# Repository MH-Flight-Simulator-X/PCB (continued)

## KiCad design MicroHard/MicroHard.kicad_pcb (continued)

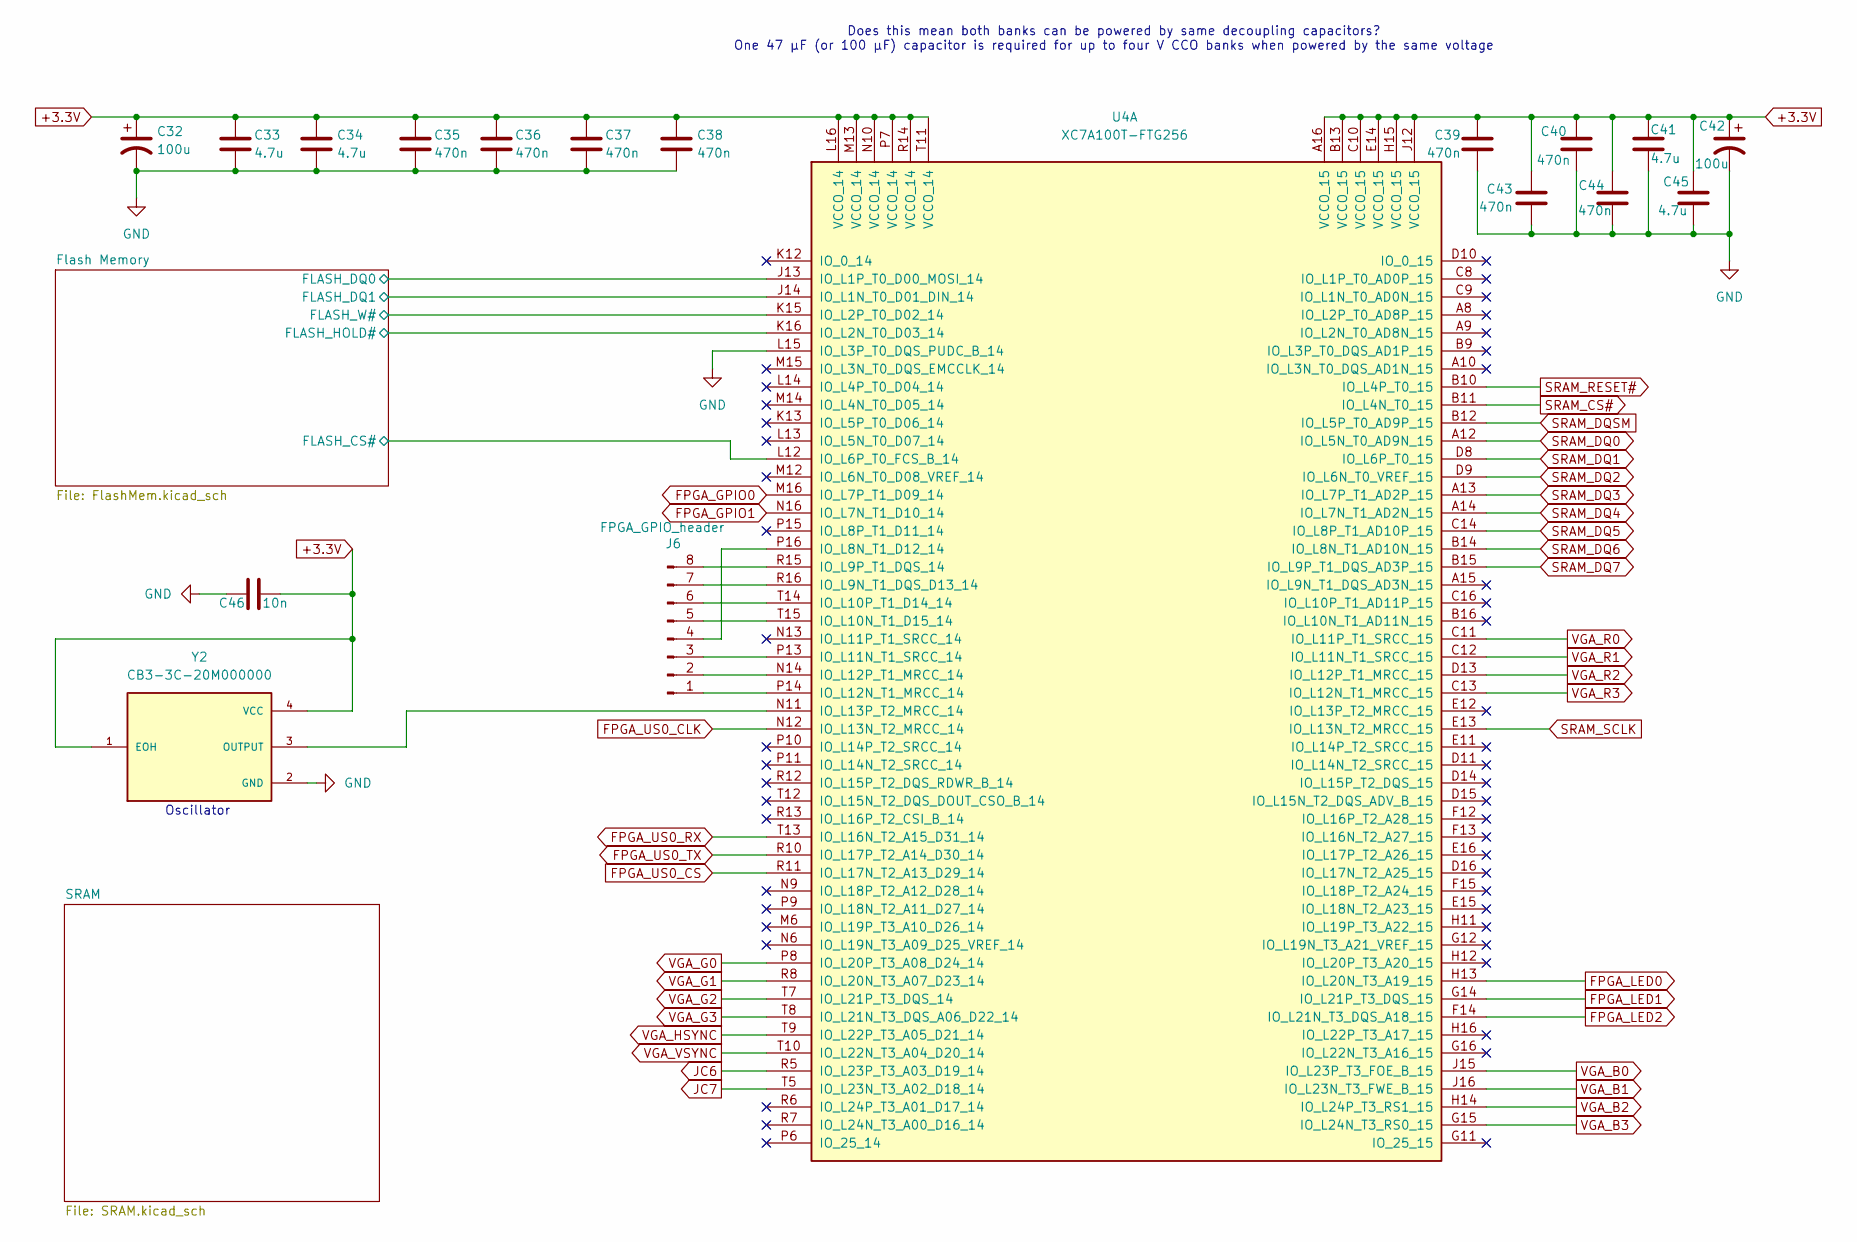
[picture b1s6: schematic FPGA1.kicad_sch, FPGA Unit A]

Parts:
C32, C42: 100u; C_1210_3225Metric_Pad1.33x2.70mm_HandSolder
C33, C34, C41, C45: 4.7u; C_0805_2012Metric_Pad1.18x1.45mm_HandSolder
C35, C36, C37, C38, C39, C40, C43, C44: 470n; C_0603_1608Metric_Pad1.08x0.95mm_HandSolder
C46: 10n; C_1206_3216Metric_Pad1.33x1.80mm_HandSolder
J6: FPGA_GPIO_header; PinHeader_1x08_P2.54mm_Vertical
U4: XC7A100T-FTG256; BGA256C100P16X16_1700X1700X155
Y2: CB3-3C-20M000000; OSC_CB3-3C-20M000000; PARTREV NA

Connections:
+3.3V: C32.1, C33.1, C34.1, C35.1, C36.1, C37.1, C38.1, C39.1, C40.1, C41.1, C42.1, C43.1, C44.1, C45.1, C46.1, U4.A16 (VCCO_15), U4.B13 (VCCO_15), U4.C10 (VCCO_15), U4.E14 (VCCO_15), U4.H15 (VCCO_15), U4.J12 (VCCO_15), U4.L16 (VCCO_14), U4.M13 (VCCO_14), U4.N10 (VCCO_14), U4.P7 (VCCO_14), U4.R14 (VCCO_14), U4.T11 (VCCO_14), Y2.1 (EOH), Y2.4 (VCC); also elsewhere on the board
/FPGA/Unit A/Flash Memory/FLASH_CS#: U4.L12 (IO_L6P_T0_FCS_B_14); also elsewhere on the board
/FPGA/Unit A/Flash Memory/FLASH_DQ0: U4.J13 (IO_L1P_T0_D00_MOSI_14); also elsewhere on the board
/FPGA/Unit A/Flash Memory/FLASH_DQ1: U4.J14 (IO_L1N_T0_D01_DIN_14); also elsewhere on the board
/FPGA/Unit A/Flash Memory/FLASH_HOLD#: U4.K16 (IO_L2N_T0_D03_14); also elsewhere on the board
/FPGA/Unit A/Flash Memory/FLASH_W#: U4.K15 (IO_L2P_T0_D02_14); also elsewhere on the board
FPGA_GPIO0: U4.M16 (IO_L7P_T1_D09_14); also elsewhere on the board
FPGA_GPIO1: U4.N16 (IO_L7N_T1_D10_14); also elsewhere on the board
FPGA_LED0: U4.H13 (IO_L20N_T3_A19_15); also elsewhere on the board
FPGA_LED1: U4.G14 (IO_L21P_T3_DQS_15); also elsewhere on the board
FPGA_LED2: U4.F14 (IO_L21N_T3_DQS_A18_15); also elsewhere on the board
FPGA_US0_CLK: U4.N12 (IO_L13N_T2_MRCC_14); also elsewhere on the board
FPGA_US0_CS: U4.R11 (IO_L17N_T2_A13_D29_14); also elsewhere on the board
FPGA_US0_RX: U4.T13 (IO_L16N_T2_A15_D31_14); also elsewhere on the board
FPGA_US0_TX: U4.R10 (IO_L17P_T2_A14_D30_14); also elsewhere on the board
GND: C32.2, C33.2, C34.2, C35.2, C36.2, C37.2, C38.2, C39.2, C40.2, C41.2, C42.2, C43.2, C44.2, C45.2, C46.2, U4.L15 (IO_L3P_T0_DQS_PUDC_B_14), Y2.2 (GND); also elsewhere on the board
JC6: U4.R5 (IO_L23P_T3_A03_D19_14)
JC7: U4.T5 (IO_L23N_T3_A02_D18_14)
unnamed: J6.1, U4.P14 (IO_L12N_T1_MRCC_14)
unnamed: J6.2, U4.N14 (IO_L12P_T1_MRCC_14)
unnamed: J6.3, U4.P13 (IO_L11N_T1_SRCC_14)
unnamed: J6.4, U4.P16 (IO_L8N_T1_D12_14)
unnamed: J6.5, U4.T15 (IO_L10N_T1_D15_14)
unnamed: J6.6, U4.T14 (IO_L10P_T1_D14_14)
unnamed: J6.7, U4.R16 (IO_L9N_T1_DQS_D13_14)
unnamed: J6.8, U4.R15 (IO_L9P_T1_DQS_14)
unnamed: U4.N11 (IO_L13P_T2_MRCC_14), Y2.3 (OUTPUT)
SRAM_CS#: U4.B11 (IO_L4N_T0_15); also elsewhere on the board
SRAM_DQ0: U4.A12 (IO_L5N_T0_AD9N_15); also elsewhere on the board
SRAM_DQ1: U4.D8 (IO_L6P_T0_15); also elsewhere on the board
SRAM_DQ2: U4.D9 (IO_L6N_T0_VREF_15); also elsewhere on the board
SRAM_DQ3: U4.A13 (IO_L7P_T1_AD2P_15); also elsewhere on the board
SRAM_DQ4: U4.A14 (IO_L7N_T1_AD2N_15); also elsewhere on the board
SRAM_DQ5: U4.C14 (IO_L8P_T1_AD10P_15); also elsewhere on the board
SRAM_DQ6: U4.B14 (IO_L8N_T1_AD10N_15); also elsewhere on the board
SRAM_DQ7: U4.B15 (IO_L9P_T1_DQS_AD3P_15); also elsewhere on the board
SRAM_DQSM: U4.B12 (IO_L5P_T0_AD9P_15); also elsewhere on the board
SRAM_RESET#: U4.B10 (IO_L4P_T0_15); also elsewhere on the board
SRAM_SCLK: U4.E13 (IO_L13N_T2_MRCC_15); also elsewhere on the board
VGA_B0: U4.J15 (IO_L23P_T3_FOE_B_15); also elsewhere on the board
VGA_B1: U4.J16 (IO_L23N_T3_FWE_B_15); also elsewhere on the board
VGA_B2: U4.H14 (IO_L24P_T3_RS1_15); also elsewhere on the board
VGA_B3: U4.G15 (IO_L24N_T3_RS0_15); also elsewhere on the board
VGA_G0: U4.P8 (IO_L20P_T3_A08_D24_14); also elsewhere on the board
VGA_G1: U4.R8 (IO_L20N_T3_A07_D23_14); also elsewhere on the board
VGA_G2: U4.T7 (IO_L21P_T3_DQS_14); also elsewhere on the board
VGA_G3: U4.T8 (IO_L21N_T3_DQS_A06_D22_14); also elsewhere on the board
VGA_HSYNC: U4.T9 (IO_L22P_T3_A05_D21_14); also elsewhere on the board
VGA_R0: U4.C11 (IO_L11P_T1_SRCC_15); also elsewhere on the board
VGA_R1: U4.C12 (IO_L11N_T1_SRCC_15); also elsewhere on the board
VGA_R2: U4.D13 (IO_L12P_T1_MRCC_15); also elsewhere on the board
VGA_R3: U4.C13 (IO_L12N_T1_MRCC_15); also elsewhere on the board
VGA_VSYNC: U4.T10 (IO_L22N_T3_A04_D20_14); also elsewhere on the board

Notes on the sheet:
Does this mean both banks can be powered by same decoupling capacitors? One 47 μF (or 100 μF) capacitor is required for up to four V CCO banks when powered by the same voltage
Oscillator

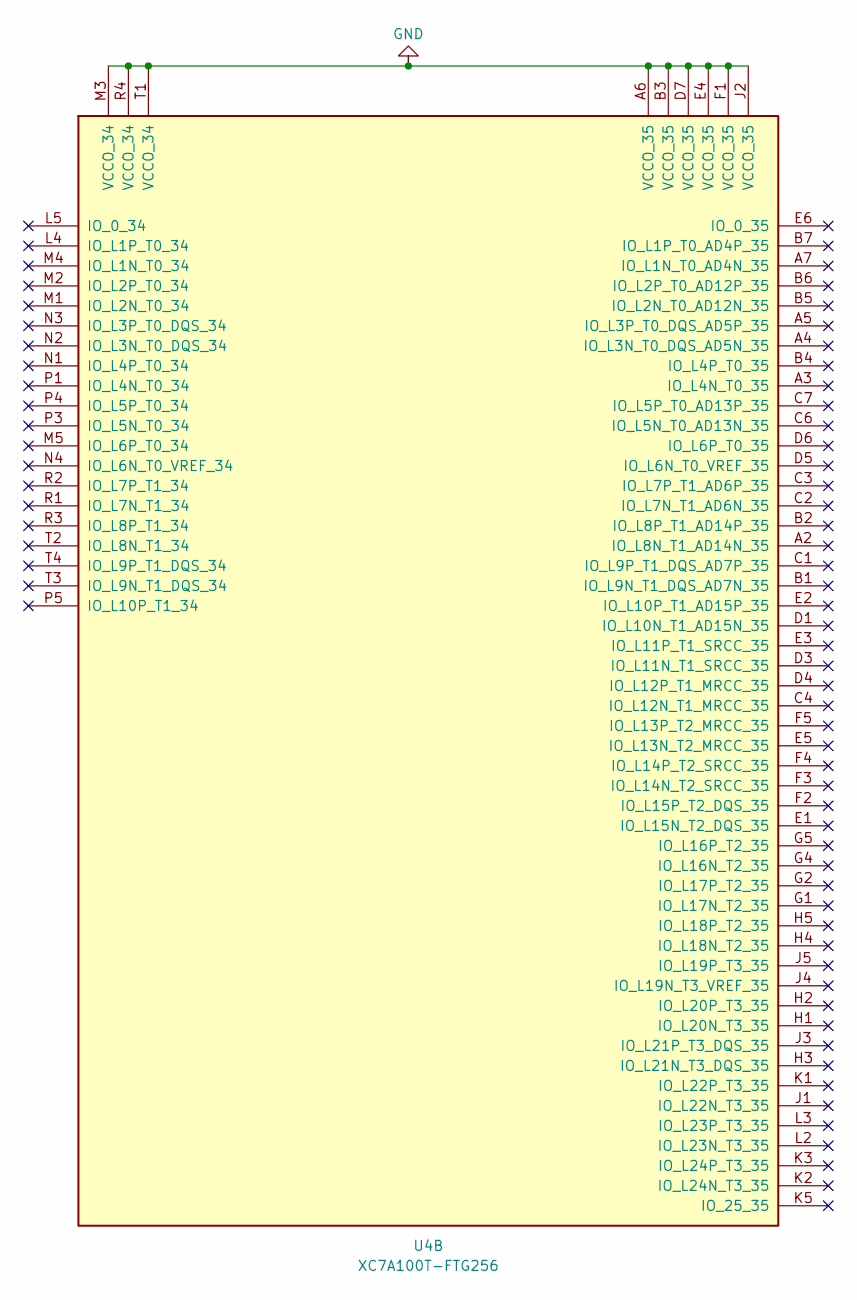
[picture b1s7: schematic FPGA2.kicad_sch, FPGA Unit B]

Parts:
U4: XC7A100T-FTG256; BGA256C100P16X16_1700X1700X155

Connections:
GND: U4.A6 (VCCO_35), U4.B3 (VCCO_35), U4.D7 (VCCO_35), U4.E4 (VCCO_35), U4.F1 (VCCO_35), U4.J2 (VCCO_35), U4.M3 (VCCO_34), U4.R4 (VCCO_34), U4.T1 (VCCO_34); also elsewhere on the board

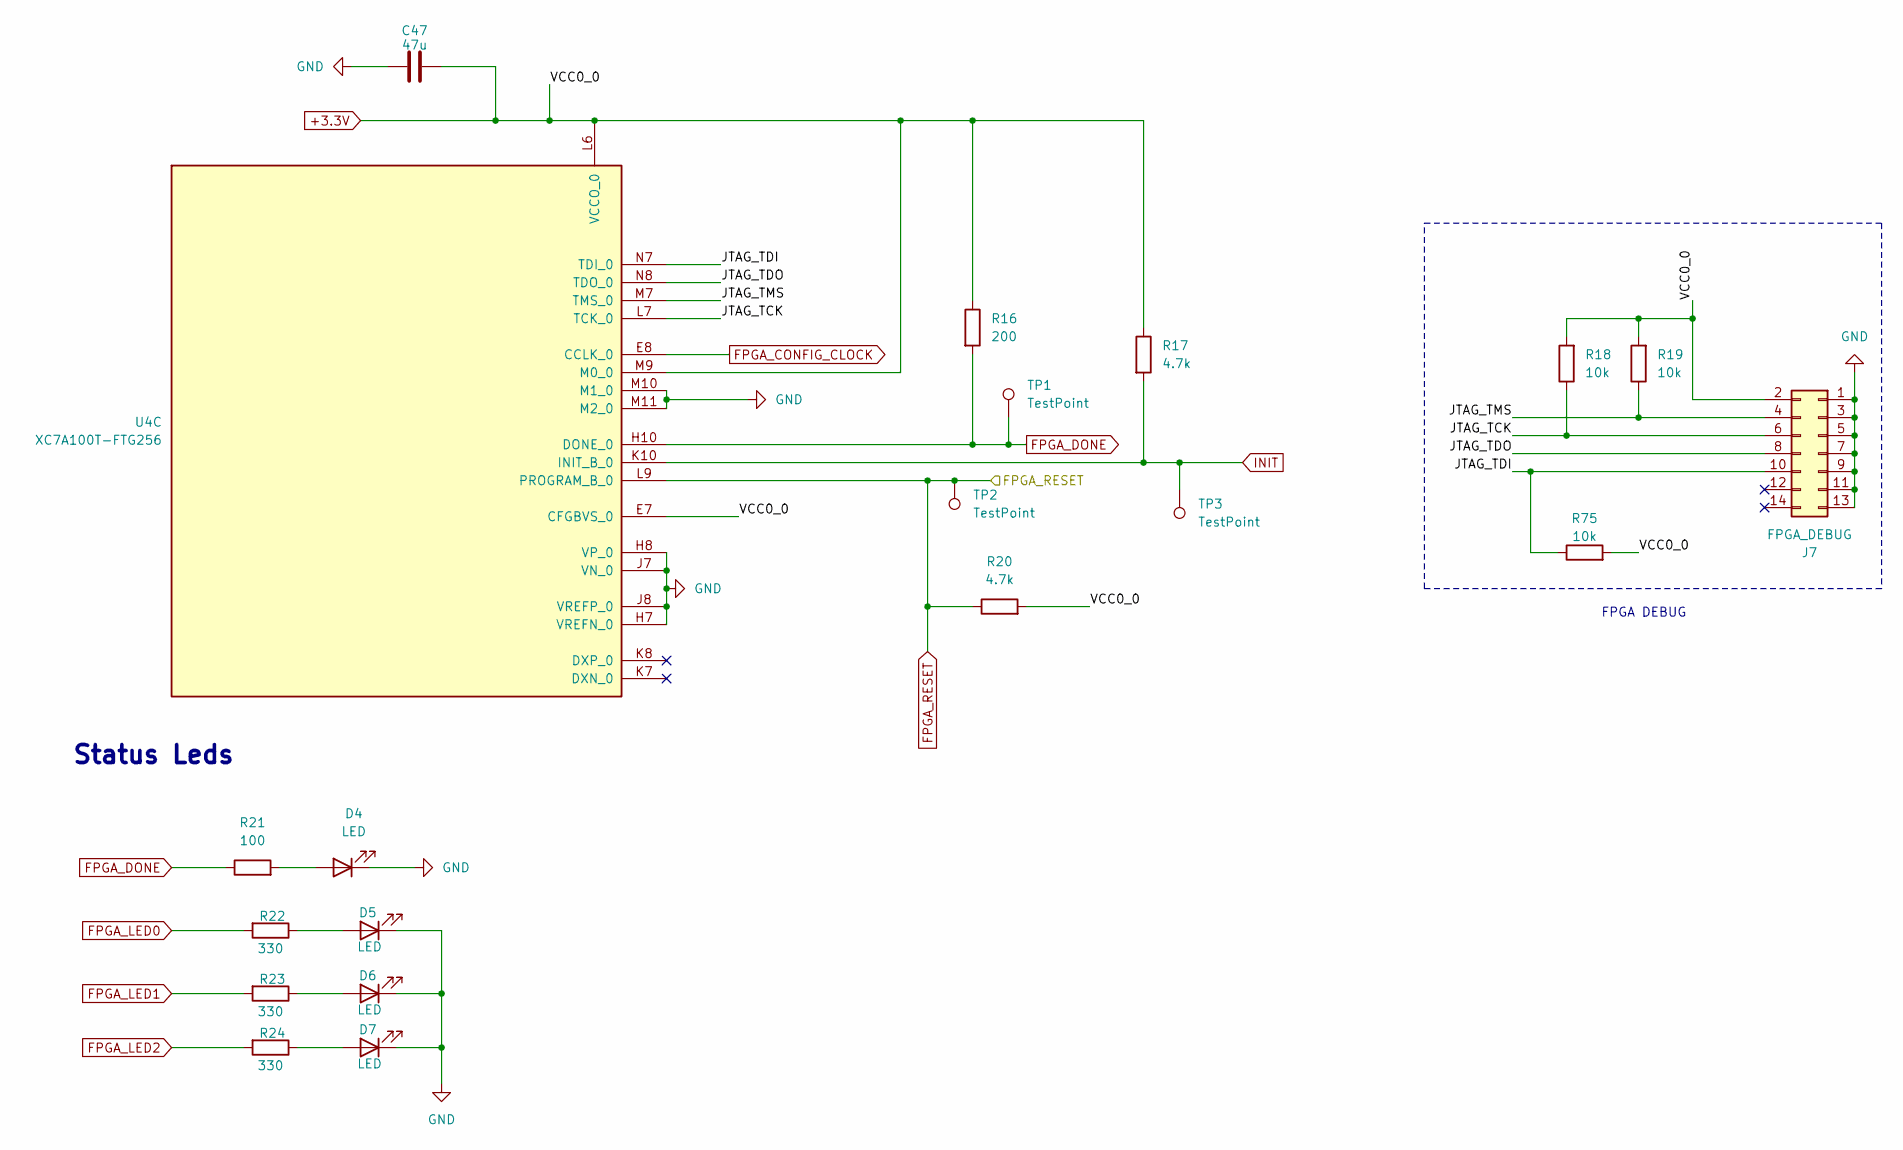
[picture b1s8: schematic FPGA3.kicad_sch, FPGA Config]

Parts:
C47: 47u; C_1210_3225Metric_Pad1.33x2.70mm_HandSolder
D4, D5, D6, D7: LED; LED_1206_3216Metric_Pad1.42x1.75mm_HandSolder
J7: FPGA_DEBUG; MOLEX_87832-1420
R16: 200; R_1206_3216Metric_Pad1.30x1.75mm_HandSolder
R17, R20: 4.7k; R_1206_3216Metric_Pad1.30x1.75mm_HandSolder
R18, R19, R75: 10k; R_1206_3216Metric_Pad1.30x1.75mm_HandSolder
R21: 100; R_1206_3216Metric_Pad1.30x1.75mm_HandSolder
R22, R23, R24: 330; R_1206_3216Metric_Pad1.30x1.75mm_HandSolder
TP1, TP2, TP3: TestPoint; TestPoint_Pad_D2.0mm
U4: XC7A100T-FTG256; BGA256C100P16X16_1700X1700X155

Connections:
+3.3V: C47.1, J7.2, R16.1, R17.1, R18.2, R19.2, R20.2, R75.2, U4.E7 (CFGBVS_0), U4.L6 (VCCO_0), U4.M9 (M0_0); also elsewhere on the board
/FPGA/FPGA Config/JTAG_TCK: J7.6, R18.1, U4.L7 (TCK_0)
/FPGA/FPGA Config/JTAG_TDI: J7.10, R75.1, U4.N7 (TDI_0)
/FPGA/FPGA Config/JTAG_TDO: J7.8, U4.N8 (TDO_0)
/FPGA/FPGA Config/JTAG_TMS: J7.4, R19.1, U4.M7 (TMS_0)
FPGA_CONFIG_CLOCK: U4.E8 (CCLK_0); also elsewhere on the board
FPGA_DONE: R16.2, R21.1, TP1.1, U4.H10 (DONE_0); also elsewhere on the board
FPGA_LED0: R22.2; also elsewhere on the board
FPGA_LED1: R23.2; also elsewhere on the board
FPGA_LED2: R24.2; also elsewhere on the board
FPGA_RESET: R20.1, TP2.1, U4.L9 (PROGRAM_B_0); also elsewhere on the board
GND: C47.2, D4.1 (K), D5.1 (K), D6.1 (K), D7.1 (K), J7.1, J7.3, J7.5, J7.7, J7.9, J7.11, J7.13, U4.H7 (VREFN_0), U4.H8 (VP_0), U4.J7 (VN_0), U4.J8 (VREFP_0), U4.M10 (M1_0), U4.M11 (M2_0); also elsewhere on the board
INIT: R17.2, TP3.1, U4.K10 (INIT_B_0)
unnamed: D4.2 (A), R21.2
unnamed: D5.2 (A), R22.1
unnamed: D6.2 (A), R23.1
unnamed: D7.2 (A), R24.1

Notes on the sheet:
FPGA DEBUG
Status Leds

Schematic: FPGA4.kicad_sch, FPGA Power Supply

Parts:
C48: 330u; CP_EIA-7343-31_Kemet-D_Pad2.25x2.55mm_HandSolder
C49, C50, C51, C52, C53, C54, C64, C65: 4.7u; C_0805_2012Metric_Pad1.18x1.45mm_HandSolder
C55, C56, C57, C58, C59, C60, C61, C62, C66, C67, C68, C70, C71: 470n; C_0603_1608Metric_Pad1.08x0.95mm_HandSolder
C63: 47u; C_1210_3225Metric_Pad1.33x2.70mm_HandSolder
C69: 100u; C_1210_3225Metric_Pad1.33x2.70mm_HandSolder
U4: XC7A100T-FTG256; BGA256C100P16X16_1700X1700X155

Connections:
+1V0: C48.1, C49.1, C50.1, C51.1, C52.1, C53.1, C54.1, C55.1, C56.1, C57.1, C58.1, C59.1, C60.1, C61.1, C62.1, C69.1, C70.1, C71.1, U4.E10 (VCCBRAM), U4.F7 (VCCINT), U4.F9 (VCCINT), U4.F11 (VCCBRAM), U4.G6 (VCCINT), U4.H9 (VCCINT), U4.J6 (VCCINT), U4.K9 (VCCINT), U4.L8 (VCCINT); also elsewhere on the board
+1V8: C63.1, C64.1, C65.1, C66.1, C67.1, C68.1, U4.G8 (VCCADC_0), U4.G10 (VCCAUX), U4.J10 (VCCAUX), U4.K11 (VCCAUX), U4.L10 (VCCAUX); also elsewhere on the board
GND: C48.2, C49.2, C50.2, C51.2, C52.2, C53.2, C54.2, C55.2, C56.2, C57.2, C58.2, C59.2, C60.2, C61.2, C62.2, C63.2, C64.2, C65.2, C66.2, C67.2, C68.2, C69.2, C70.2, C71.2, U4.A1 (GND), U4.A11 (GND), U4.B8 (GND), U4.C5 (GND), U4.C15 (GND), U4.D2 (GND), U4.D12 (GND), U4.E9 (GND), U4.F6 (GND), U4.F8 (VCCBATT_0), U4.F10 (GND), U4.F16 (GND), U4.G3 (GND), U4.G7 (GNDADC_0), U4.G9 (GND), U4.G13 (GND), U4.H6 (GND), U4.J9 (GND), U4.J11 (GND), U4.K4 (GND), U4.K6 (GND), U4.K14 (GND), U4.L1 (GND), U4.L11 (GND), U4.M8 (GND), U4.N5 (GND), U4.N15 (GND), U4.P2 (GND), U4.P12 (GND), U4.R9 (GND), U4.T6 (GND), U4.T16 (GND); also elsewhere on the board

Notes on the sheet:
On the physical board the smallest capacitors must be closest to the power input

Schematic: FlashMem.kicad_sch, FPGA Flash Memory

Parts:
C80: 100n; C_1206_3216Metric_Pad1.33x1.80mm_HandSolder
R69, R71: 4.7k; R_1206_3216Metric_Pad1.30x1.75mm_HandSolder
R70: 2.4k; R_1206_3216Metric_Pad1.30x1.75mm_HandSolder
U8: MT25QL256ABA8ESF-0SIT; SOIC127P1032X265-16N

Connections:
+3.3V: C80.1, R69.1, R70.1, R71.1, U8.2 (Vcc); also elsewhere on the board
/FPGA/Unit A/Flash Memory/FLASH_CS#: R70.2, U8.7 (S#); also elsewhere on the board
/FPGA/Unit A/Flash Memory/FLASH_DQ0: U8.15 (DQ0); also elsewhere on the board
/FPGA/Unit A/Flash Memory/FLASH_DQ1: U8.8 (DQ1); also elsewhere on the board
/FPGA/Unit A/Flash Memory/FLASH_HOLD#: R69.2, U8.1 (DQ3/HOLD#); also elsewhere on the board
/FPGA/Unit A/Flash Memory/FLASH_W#: R71.2, U8.9 (W#/DQ2); also elsewhere on the board
FPGA_CONFIG_CLOCK: U8.16 (C); also elsewhere on the board
GND: C80.2, U8.10 (Vss); also elsewhere on the board

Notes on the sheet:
Flash Memory

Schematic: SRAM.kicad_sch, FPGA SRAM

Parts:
C81: 100n; C_1206_3216Metric_Pad1.33x1.80mm_HandSolder
IC1: IS66WVO32M8DBLL-166BLI; BGA24C100P5X5_600X800X120; Mouser Part Number 870-IS66W8DBLL166BLI
R72, R73: 2.4k; R_1206_3216Metric_Pad1.30x1.75mm_HandSolder

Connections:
+3.3V: C81.1, IC1.B4 (VCC), IC1.D1 (VCCQ_1), IC1.E4 (VCCQ_2), R72.2, R73.2; also elsewhere on the board
GND: C81.2, IC1.B3 (VSS), IC1.C1 (VSSQ_1), IC1.E5 (VSSQ_2); also elsewhere on the board
SRAM_CS#: IC1.A3 (CS#), R72.1; also elsewhere on the board
SRAM_DQ0: IC1.D3 (SIO0); also elsewhere on the board
SRAM_DQ1: IC1.D2 (SIO1); also elsewhere on the board
SRAM_DQ2: IC1.C4 (SIO2); also elsewhere on the board
SRAM_DQ3: IC1.D4 (SIO3); also elsewhere on the board
SRAM_DQ4: IC1.D5 (SIO4); also elsewhere on the board
SRAM_DQ5: IC1.E3 (SIO5); also elsewhere on the board
SRAM_DQ6: IC1.E2 (SIO6); also elsewhere on the board
SRAM_DQ7: IC1.E1 (SIO7); also elsewhere on the board
SRAM_DQSM: IC1.C3 (DQSM); also elsewhere on the board
SRAM_RESET#: IC1.A4 (RESET#), R73.1; also elsewhere on the board
SRAM_SCLK: IC1.B2 (SCLK); also elsewhere on the board

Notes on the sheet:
PSRAM
Didnt specify capacitor

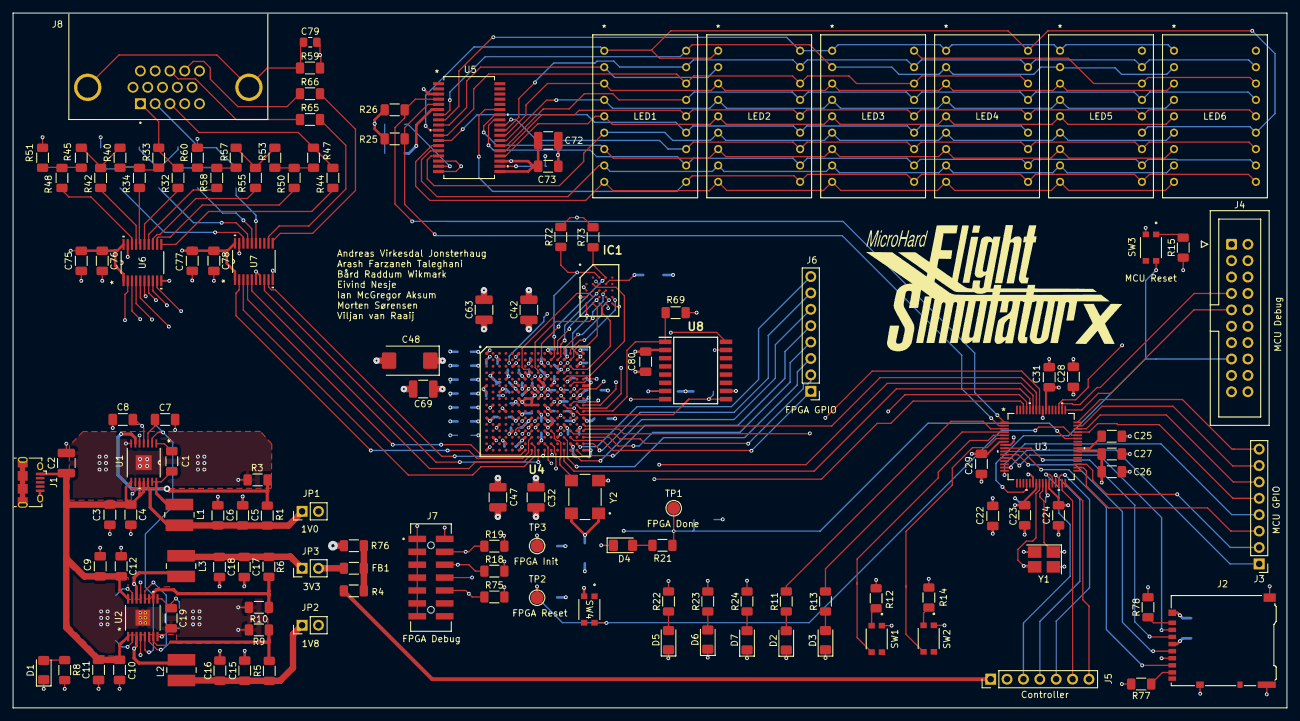
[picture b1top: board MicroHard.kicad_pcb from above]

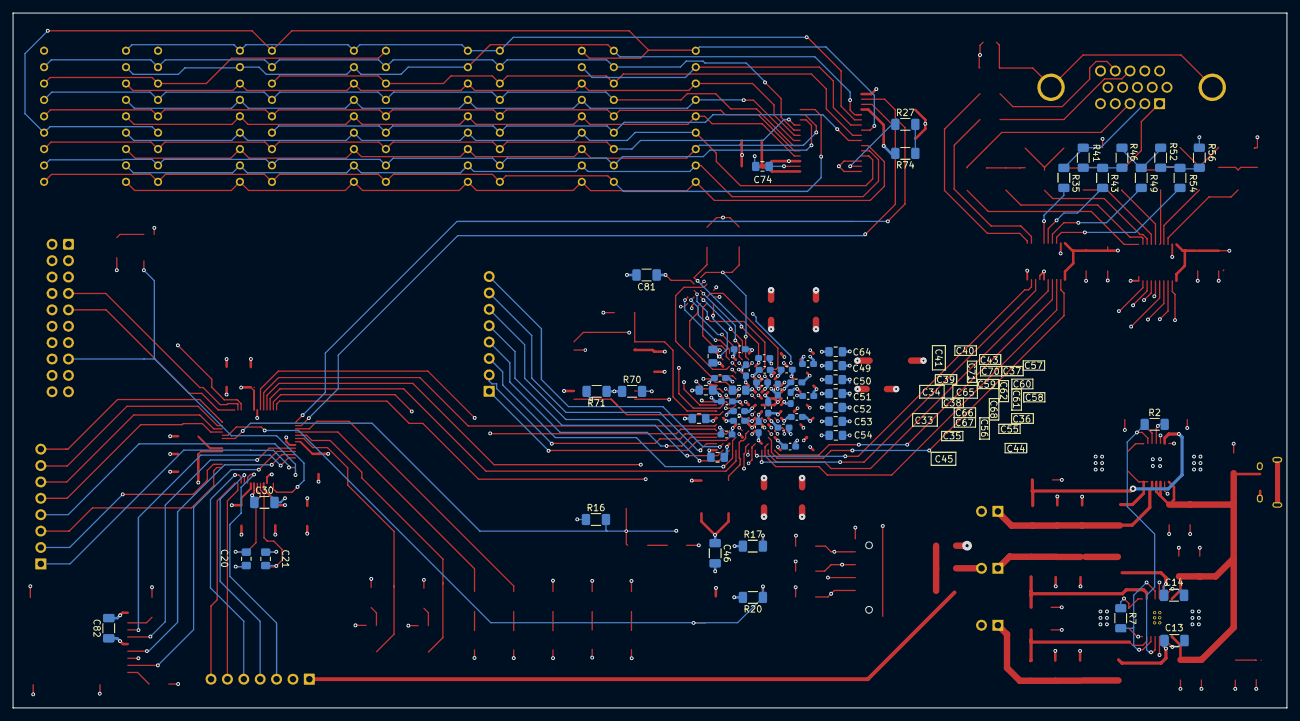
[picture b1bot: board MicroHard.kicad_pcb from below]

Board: 6 copper layers, 197.5 x 107.7 mm, 192 parts (59 on the bottom side), 175 nets.

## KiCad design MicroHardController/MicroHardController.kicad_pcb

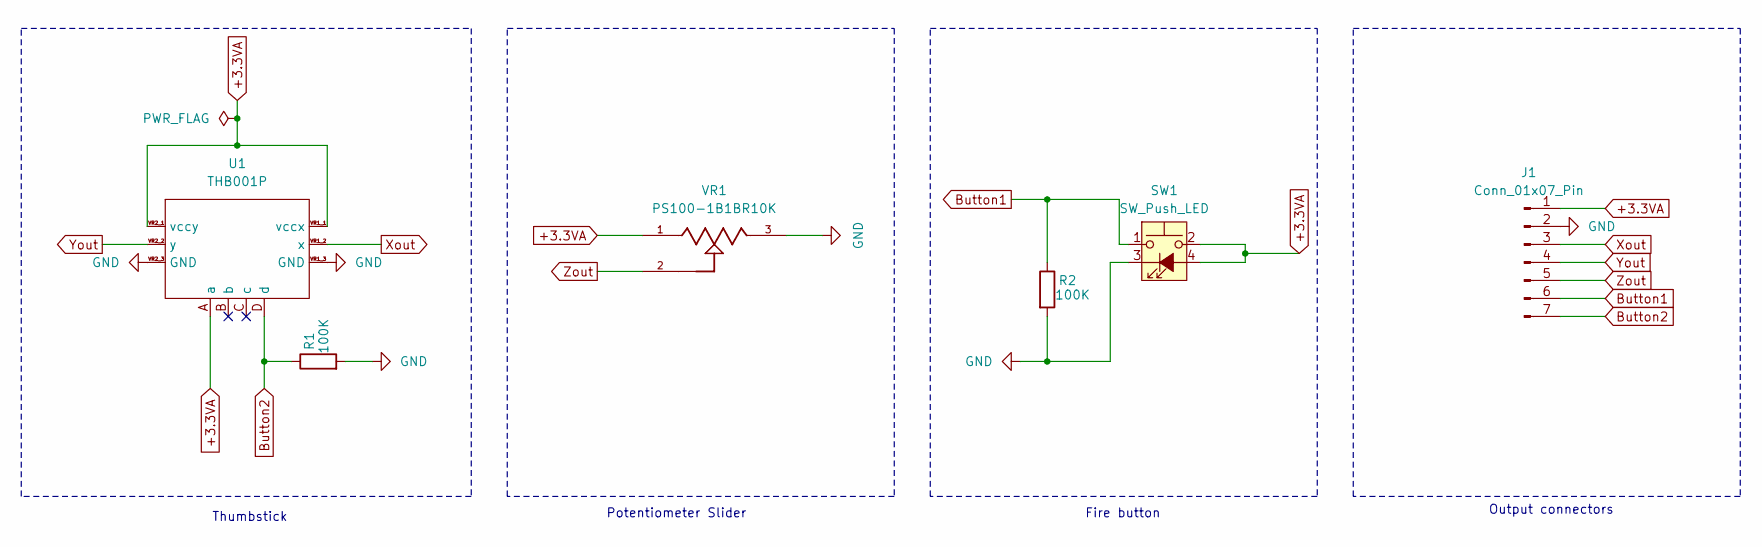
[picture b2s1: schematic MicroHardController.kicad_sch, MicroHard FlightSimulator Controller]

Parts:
J1: Conn_01x07_Pin; PinHeader_1x07_P2.54mm_Vertical
R1, R2: 100K; R_1206_3216Metric_Pad1.30x1.75mm_HandSolder
SW1: SW_Push_LED; PinHeader_1x04_P2.54mm_Vertical
U1: THB001P; CNK_THB001P
VR1: PS100-1B1BR10K; TRIM_PS100-1B1BR10K; PARTREV B

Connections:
+3.3VA: J1.1, SW1.2, SW1.4 (A), U1.A (a), U1.VR1_1 (vccx), U1.VR2_1 (vccy), VR1.1
Button1: J1.6, R2.1, SW1.1
Button2: J1.7, R1.1, U1.D (d)
GND: J1.2, R1.2, R2.2, SW1.3 (K), U1.VR1_3 (GND), U1.VR2_3 (GND), VR1.3
Xout: J1.3, U1.VR1_2 (x)
Yout: J1.4, U1.VR2_2 (y)
Zout: J1.5, VR1.2

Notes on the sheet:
Fire button
Thumbstick
Output connectors
Potentiometer Slider

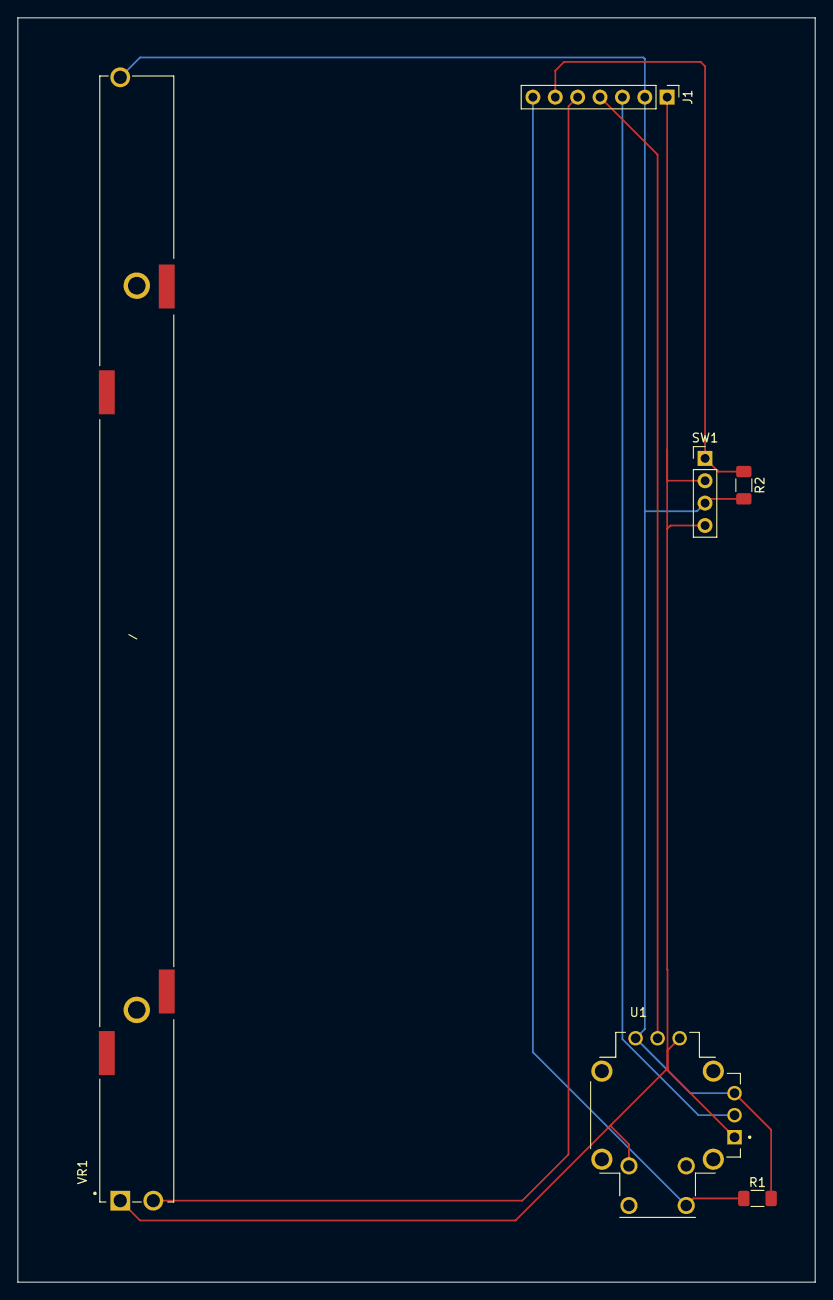
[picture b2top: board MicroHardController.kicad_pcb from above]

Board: 2 copper layers, 90.5 x 143.5 mm, 6 parts (0 on the bottom side), 7 nets.

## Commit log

2024-09-06 feat: powersupply started
2024-09-07 feat: powersupply
2024-09-07 feat: finished power supply
2024-09-08 feat: added jumper
2024-09-08 fix: powersupply passes ERV
2024-09-08 feat: microhard controller schematic
2024-09-08 feat: controller pcb layout
2024-09-09 feat: added EFM32GG842... schematic symbol
2024-09-11 Add mcu symbol and footprint
2024-09-17 feat: added fpga
2024-09-19 extra files
2024-09-22 feat: finished FPGA config
2024-09-23 feat: finished Flash mem and FPGA Config
2024-09-24 feat: finished config
2024-09-24 MCU schematic
2024-09-24 Fix library paths
2024-09-24 chore
2024-09-24 feat: added VGA signal out from FPGA
2024-09-24 feat: VGA out lines from FPGA drawn
2024-09-25 feat: finished schematic, TODO: go through checklist
2024-09-26 feat: completed schematic draft
2024-09-26 Finish display
2024-09-26 Renumber parts
2024-09-26 merged
2024-09-26 Add missing footprint libs
2024-09-26 fix: controller fix
2024-09-26 Add Controller Btn 2 to MCU
2024-09-26 footprints
2024-09-26 added VGA footprint
2024-09-26 Small fixes
2024-09-27 Initial layout
2024-09-27 VGA and Display layout
2024-09-27 feat: controller fixed
2024-09-27 power plane
2024-09-28 Power supply layout
2024-09-28 Add MCU
2024-09-29 finished memory
2024-09-29 wired up VGA
2024-09-30 finished FPGA
2024-09-30 finished layout
2024-09-30 Clean up
2024-09-30 Fix vias
2024-09-30 final fix
2024-10-01 Final changes
2024-10-01 Change inductor footprint
2024-10-01 Fix wrong display pin connection
2024-10-01 Add connector labels to silkscreen
2024-11-06 feat: logo first draft
2024-11-06 feat: 2 different controller variants
2024-11-06 IDK what this commit does, best to ignore it tb tbj
2024-11-10 feat: tbh dont know what this does, but fuck it we ball
2024-11-19 feat: finished PCB case design
2024-11-20 Fix schematics for delivery
2024-11-20 feat: added controller case SCAD files
